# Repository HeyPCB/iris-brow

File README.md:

# Iris Brow

The forehead sensor strip of Iris: a VL53L1X distance sensor for vergence, an APDS-9306 light sensor, two I2S microphones 108 mm apart for sound direction and touch pads, on a brow-shaped board.

Part of [Iris, the human-eyed robot head](https://github.com/HeyPCB/iris), HeyPCB's open robot boards. Designed end to end with the HeyPCB method on
KiCad 10 (headless pipeline, Freerouting 2.4.1); every number below is measured on the files in this repository.
Mentions of `./run.sh`, `docs/rules/`, `blocks/` or `parts/` refer to the heypcb-kicad SDK that produced them.

| Layers | Outline | Parts | Nets | Connections routed | Vias | ERC errors | DRC errors / unconnected / parity |
|---|---|---|---|---|---|---|---|
| 2 | 116 x 12 mm, shaped | 20 | 11 | 45 -> 0 open | 33 | 0 | 0 / 0 / 0 |

**Not fabricated, assembled or powered.**

| | |
|---|---|
| KiCad project | [`kicad/`](kicad/) |
| Gerbers (unzipped and zipped), BOM, CPL, STEP, schematic PDF | [`fab/`](fab/) |
| Mechanism CAD, fit check and system docs | [Iris, the human-eyed robot head](https://github.com/HeyPCB/iris) |
| Renders | [top](media/top.png), [bottom](media/bottom.png) |
| Design process, every step as KiCad rendered it | [`media/design-process.mp4`](media/design-process.mp4) |

Iris Brow is the forehead sensor strip of **Iris**, an open-hardware robot head with human-like eyes. It
is board B4 of the Iris system spec v0.1 (section 4.3). The strip is 116 x 12 mm and sits behind the
forehead shell. It carries:
- a time-of-flight sensor for vergence distance;
- an ambient light sensor;
- two I2S microphones 108 mm apart, for the direction of a sound;
- a touch electrode.

One 8-pin JST SH harness connects it to the Cortex board (B1, ESP32-S3). It was designed with the HeyPCB
method on KiCad 10.0.6, by heypcb-kicad's headless pipeline with Freerouting 2.4.1, from the brief in
`board.json`.

**This board has not been fabricated, assembled or powered.** Everything below is what KiCad and the
pipeline measured on the design files. Nothing here has been tested on hardware or in the head. Gate
numbers come from `report.json`, positions and track lengths from
`coords.json` (written by `boards/iris_brow/coords.py`). Both come from the full run of
2026-10-03.

## Role in Iris

Iris has four board designs (spec section 4). B1 Cortex rides on the tilt cradle and runs the
ESP32-S3. B2 Brainstem is the power and servo hub. B3 is the iris LED ring, one in each eye. B4 Brow is
fixed to the forehead shell and adds what the eyes lack (spec section 4):

- **Distance for vergence.** The VL53L1X measures the distance d to the face in front of the robot.
  Firmware sets the vergence angle from it: vergence = 2 atan(39 / d) for the 78 mm IPD (spec section 8).
- **Ambient light.** It sets the brightness of the iris glow and the blink rate.
- **Stereo hearing for orienting saccades.** The two microphones are exactly 108 mm apart (head Y
  -54 and +54). That gives a maximum time difference of 0.31 ms, about 15 samples at 48 kHz (spec
  section 8, GCC-PHAT).
- **A forehead touch pad** for a "pat" reaction (ESP32-S3 TOUCH14).

## Features

- **ST VL53L1X** time-of-flight sensor (U1, VL53L1CXV0FY/1). It ranges up to 4 m with a field of view
  of up to 27 degrees, at up to 50 Hz (ST DocID031281 Rev 3, p.1 and Table 1). It sits on the centre
  line, on the face side.
  - ST's 100 nF and 4.7 uF are next to its AVDDVCSEL and AVSSVCSEL pins.
  - XSHUT is tied high through 10k, because it is not on the harness.
  - GPIO1 (the interrupt) is not connected, as the datasheet allows when it is unused.
- **Broadcom APDS-9306-065** ambient light sensor (U2), on the centre line above the ToF, with its
  datasheet 1 uF. Its INT output is not connected; firmware polls it.
- **Two TDK ICS-43434** bottom-port I2S microphones (MK1, MK2). They sit on the inside face and their
  0.5 mm sound ports open through the board at exactly x 4.0 and 112.0.
  - MK1 is MIC L (robot left). Its LR pin is low, so it answers in the **left** I2S slot.
  - MK2 is MIC R (robot right). Its LR pin is high, so it answers in the **right** slot.
  - Each has 100 nF at VDD and drives the shared SD line through 33 ohm.
- **Touch electrode:** two mirror-image 10 x 5 mm exposed copper pads (TP1 and TP2) on one TOUCH net,
  either side of the centre sensors. Espressif's keep-outs are board rule areas:
  - nothing on the opposite face;
  - a 1.5 mm gap to any ground or track;
  - a 0.15 mm trace.
- **J1:** JST SH 8-pin side-entry header SM08B-SRSS-TB, centred on the inside face with its mouth up.
  It is pinned exactly as the spec's BROW contract. A 10 uF bulk capacitor on 3V3 (C6) sits beside the
  ToF.
- **Board:**
  - a brow-shaped outline inside the binding 116 x 12 mm envelope, symmetric about the centre line;
  - 2 layers, 1.6 mm;
  - GND poured on both faces after routing;
  - four M2 holes at the binding positions.
- 20 footprints: 14 assembled parts, 2 copper touch pads (DNP), 4 holes. No regulator: 3V3 comes from
  the Cortex board.
- **3V3 load, from the datasheets** (a sum, not a measurement): about 19 mA on average, 41 mA at the
  ToF's emitter peaks. That is inside the contract's 50 mA. The parts are:
  - VL53L1X: 16-18 mA ranging average, peaks up to 40 mA (ST Table 16);
  - APDS-9306: 85 uA;
  - two ICS-43434: 490 uA each (TDK DS-000069, high-performance mode).

## Block diagram

```mermaid
flowchart LR
  B1["B1 Cortex: ESP32-S3<br/>J4 SH-8"]
  subgraph B4["B4 Iris Brow: 116 x 12 mm, 2 layers"]
    J1["J1 SM08B-SRSS-TB<br/>C6 10 uF on 3V3"]
    U1["U1 VL53L1X ToF<br/>I2C 0x29"]
    U2["U2 APDS-9306-065 ALS<br/>I2C 0x52"]
    MK1["MK1 ICS-43434, MIC L<br/>LR low: left slot"]
    MK2["MK2 ICS-43434, MIC R<br/>LR high: right slot"]
    TP["TP1 + TP2<br/>touch wings"]
  end
  B1 <-->|"BROW harness, 150 mm:<br/>3V3, GND, I2C, I2S, TOUCH"| J1
  J1 -->|"I2C_SDA, I2C_SCL, 3V3"| U1
  J1 -->|"I2C_SDA, I2C_SCL, 3V3"| U2
  J1 -->|"I2S_BCLK, I2S_WS, 3V3"| MK1
  J1 -->|"I2S_BCLK, I2S_WS, 3V3"| MK2
  MK1 -->|"SD via 33 ohm"| J1
  MK2 -->|"SD via 33 ohm"| J1
  TP -->|"TOUCH"| J1
```

## Sensor placement and windows

Board coordinates use the brief frame: mm from the board origin, x to the right and y down, seen from
the F face. Head coordinates use the spec's binding mapping (section 4.3):
- the F face is at X_H = +22.0 and faces the forehead shell;
- Y_H = x - 58;
- Z_H = 56 - y.

The shell's inner surface is at least 2.0 mm in front of the F face. Window sizes are the spec's
suggestions (section 4.3); the centres are measured from the built board.

| Feature | Board x, y (mm) | Head Y_H, Z_H (mm) | Face | Window in the shell (spec 4.3) | Where the centre comes from |
|---|---|---|---|---|---|
| VL53L1X package centre (U1) | 58.00, 6.00 | 0.00, 50.00 | F | one 6 x 3.5 mm slot centred here, or two 2.5 mm holes at the two points below | U1's placement |
| VL53L1X emitter (EMT, 0.70 mm aperture) | 56.48, 6.00 | -1.52, 50.00 | F | (inside the slot) | ST outline drawing through U1's placement |
| VL53L1X receiver (RTN, 0.85 mm lens) | 59.48, 6.00 | +1.48, 50.00 | F | (inside the slot) | ST outline drawing through U1's placement |
| APDS-9306 active area (U2) | 58.00, 2.12 | 0.00, 53.88 | F | 2 mm hole | Broadcom outline (0.223 mm off U2's centre at 58.00, 1.90) |
| MIC R sound port (MK2) | 4.00, 6.00 | -54.00, 50.00 | port through the board, part on B | 1.0 mm hole and a foam gasket ring | the footprint's 0.5 mm NPTH, measured |
| MIC L sound port (MK1) | 112.00, 6.00 | +54.00, 50.00 | port through the board, part on B | 1.0 mm hole and a foam gasket ring | the footprint's 0.5 mm NPTH, measured |
| Touch TP1 (robot right) | x 39.0-49.0, y 1.25-6.25 | Y -19.0 to -9.0, Z 54.75 to 49.75 | F, exposed copper | none (see *Check before ordering*) | pad copper, measured |
| Touch TP2 (robot left) | x 67.0-77.0, y 1.25-6.25 | Y +9.0 to +19.0, Z 54.75 to 49.75 | F, exposed copper | none | pad copper, measured |

**How the windows are marked on the board.** The SDK has no brief key for free drawings on the silk or
Fab layers, and its code was not changed. So each window is marked in four ways:
- **A named rule area on F.Cu that also bans the pour.** The F face therefore shows a bare-laminate
  patch of the window's shape round each sensor:
  - `window_tof_slot_6x3.5` (x 55.0-61.0, y 4.25-7.75; no via, no pour);
  - `window_als_d2` (2.4 mm circle at 58.00, 2.12; no via, no pour);
  - `window_mic_r_port_seal` and `window_mic_l_port_seal` (5 mm circles at the ports; no track, via
    or pour, so a gasket seals on flat mask).
- **The parts' own F.Fab outlines and values**, where the footprint has them.
- **The microphones' NPTH ports**, which go through the board.
- **The silk words "TOUCH"** beside the two pads.

"TOF" and "ALS" are in the brief's silk words, but found no free spot. A 0.8 mm word's text box is
1.47 mm tall, and the gap between the two sensors is 1.3 mm; capacitors and vias hold their other
sides. The drawing above and `coords.json` carry every number.

**Mounting and outline (binding positions kept).**
- Four 2.2 mm NPTH holes for M2 screws, at (12, 6), (34, 6), (82, 6) and (104, 6). In the head frame
  that is Y_H -46, -24, +24, +46 at Z_H +50.0. The screws go in from the B side into bosses on the shell,
  whose tips touch the F face.
- Copper, tracks and vias stay out of a 5.6 mm circle round each hole on both faces.
- The outline stays inside the spec's 116.0 x 12.0 mm envelope and is symmetric about x = 58.
  - Top edge: y = 1.0 ((x - 58) / 58)^2.
  - Bottom edge: y = 12 - 2.0 ((x - 58) / 58)^2.
  - Both are sampled every 14.5 mm and filleted (1000 mm and 600 mm on the shallow vertices, 2 mm at
    the four ends). So the strip is 12.0 mm tall at the centre and 9.0 mm at the ends.
  - The measured Edge.Cuts box is x -0.05 to 116.05 and y -0.04 to 12.03 (it includes the 0.1 mm
    line).
- **J1** is centred on the B face at (58.00, 3.35), with its mouth at y 0.73 (Z_H 55.27), so the plug
  enters from above (+Z). Pin 1 is at x 54.5 (Y_H -3.5) and pin 8 at x 61.5 (Y_H +3.5).

**Heights.** These come from the datasheets and the catalogue; none of them is a measurement.
- F face: VL53L1X 1.56 mm (the tallest; spec limit 1.6 mm), APDS-9306-065 0.65 mm, 0402 and 0603
  passives.
- B face: the SM08B-SRSS-TB body (the JLC row lists 2.9 mm and 4.32 mm), ICS-43434 0.98 mm (spec limit
  4.5 mm). `fab/iris_brow.step` has the board with KiCad's 3D bodies. U2 has no body:
  KiCad 10.0.6 ships no model for `OptoDevice:Broadcom_DFN-6_2x2mm_P0.65mm`.

## Pinout: J1 to Cortex J4 (spec section 5, BROW, binding)

JST SH 8-pin, SM08B-SRSS-TB (C160407). Pin n is pad n of the KiCad footprint. The harness is
double-ended, same direction (pin n to pin n), 28 AWG, 150 mm. The board nets below were read back from
the run's `build/iris_brow/design.json`.

| Pin | Net | Dir | Level / type | On this board |
|---|---|---|---|---|
| 1 | 3V3 | B1 -> B4 | 3.3 V, at most 50 mA (source B1 U2) | U1 AVDD/AVDDVCSEL, U2 VDD, MK1/MK2 VDD, MK2 LR, XSHUT pull-up, C6 10 uF |
| 2 | GND | | | ground; J1's two mounting pads are GND too |
| 3 | I2C_SDA | <-> | 3.3 V open drain, 400 kHz | U1 pin 9, U2 pin 2. No pull-up here: 2.2 k on B1 only |
| 4 | I2C_SCL | B1 -> | 3.3 V open drain | U1 pin 10, U2 pin 1 |
| 5 | I2S_BCLK | B1 -> B4 | 3.3 V, 3.072 MHz | MK1 and MK2 SCK |
| 6 | I2S_WS | B1 -> B4 | 3.3 V, 48 kHz | MK1 and MK2 WS |
| 7 | I2S_MIC_SD | B4 -> B1 | 3.3 V, tri-stated per slot | MK1 and MK2 SD, each through 33 ohm. The 100 k pull-down is on B1 (GPIO40) |
| 8 | TOUCH | B4 -> B1 | analog, capacitive | TP1 and TP2 (B1 GPIO14, TOUCH14) |

## I2C addresses and I2S slots

| Device | Board | 7-bit address | Note |
|---|---|---|---|
| INA226 | B2 | 0x40 | spec section 4.3 |
| VL53L1X (U1) | B4 | **0x29** | ST writes it as **0x52**, the 8-bit write address (datasheet section 4, Figure 12). Use 0x29 in a 7-bit API, or it lands on the APDS-9306 |
| APDS-9306-065 (U2) | B4 | **0x52** | fixed ("single slave address of 0X52 hex using 7-bit addressing", Broadcom AV02-4755EN) |

No two addresses collide. The camera's SCCB is on its own pins on B1.

| Microphone | Position | LR | I2S slot |
|---|---|---|---|
| MK1, MIC L | robot left, Y_H +54.0 | GND | left: data after WS falls |
| MK2, MIC R | robot right, Y_H -54.0 | 3V3 | right: data after WS rises |

Each frame has 64 SCK cycles (TDK DS-000069), so BCLK is 48 kHz x 64 = 3.072 MHz.

## Departures from the spec

| Spec (section 4.3) | On the board | Why |
|---|---|---|
| Rectangle, 116.0 x 12.0 mm, fillet 2.0 | A brow-shaped outline inside the same envelope (12 mm tall at the centre, 9 mm at the ends), with the same holes | The task asked for a gently shaped brow strip. Anything drawn for the rectangle still clears it |
| Touch electrode at x 40-52, masked F copper, with a ground-hatched ring | Two 10 x 5 mm exposed pads at x 39-49 and 67-77; no pour within 1.5 mm, nothing on B under them, solid GND pour beyond | Symmetry: a pat anywhere across the middle of the forehead lands on it. The shell is at least 2.0 mm in front of the board, and Espressif says to remove air gaps or bridge them with springs, which needs an exposed pad. KiCad's stock wire and test pads all open the mask. The SDK pours solid copper only, so there is no hatched ring |
| APDS-9306 at x 65-67 | At x 58 (centre line), y 1.9, above the ToF | A symmetric layout about the centre line |
| J1 at x 86-98 on B | Centred on B (x 52-64), mouth up | A symmetric B face, equal I2S runs to both microphones, and the shortest harness path |
| Microphone SD pins tied directly (datasheet stereo figure) | 33 ohm source resistor on each | KiCad types SD as an output, so ERC refuses two on one net. The resistor also damps the shared line |
| ICS-43434 orientation not stated | Ports outboard, pads inboard | The pads face the rest of the board. Routing closed only once each microphone's bypass capacitor had its GND pad beside the port's GND ring (MIC R's LR pin is 3V3, so its ring has no other GND neighbour) |
| (not in the spec) | 10 uF on 3V3 | Bulk at the end of the 150 mm cable for the ToF's emitter pulses (40 mA peak, ST Table 16) |

## Measured gates (full run with media, 2026-10-03, from `report.json`)

| Gate | Result |
|---|---|
| Composition | 7 block instances (6 distinct blocks, all new, prefixed `brow_`): 20 parts, 11 nets, 4 no-connects (U1 GPIO1, U1 DNC, U2 INT, U2 NC) |
| Part binding (`parts/lcsc_pinned.json`) | 14 of 14 orderable parts bound, 0 unsourced, 0 identity conflicts. H1-H4 are not in the BOM; TP1 and TP2 are DNP (copper only). 4 distinct Extended parts (C160407, C190004, C2649498, C5656610), about $12 in JLC loading fees |
| ERC (`kicad-cli sch erc --severity-all`) | **0 errors, 0 warnings** |
| Netlist round trip | **identical**, 11 nets |
| Freerouting, rung 1, fanout off (kept) | 45 -> 4 open (all GND). The last-mile router closed all 4, and DRC kept them: **0 open** |
| Freerouting, rung 1, fanout on (for comparison) | 45 -> 8 open; the last mile closed 5, so 3 open |
| Copper | 204 tracks, 28 routing vias, 732.5 mm of track (B.Cu 467.8 mm, F.Cu 264.7 mm). No net class was narrowed |
| Pours (only after a measured 0 open) | GND on F.Cu and B.Cu, 5 stitching vias (33 vias in all). 0 open after the pour, after stitching and at the end |
| Silkscreen | 3 words placed (TOUCH, TOUCH, BROW); the 4 title lines on B; 12 designators re-seated and 5 hidden; 0 stitching vias displaced |
| DRC (`--severity-all --schematic-parity`, KiCad 10.0.6) | fresh, **0 errors, 0 warnings, 0 unconnected, 0 parity** |
| DFM (`jlcpcb_2layer`) | **0 errors**, 1 warning: 45 stock-footprint silk strokes at 0.12 mm, which the fab prints at its 0.15 mm minimum |
| Fab gate | **ready**, no blockers. Two copper gerbers; the gerber job has `LayerNumber` 2 and a 1.6 mm board. The BOM has 10 rows and 14 parts; the JLC CPL lists 14 parts (7 on the bottom) and corrected 4 rotations |
| Media | 63 3D frames, the renders, and a 97.7 s video (142 frames) |

Routing depends on the last mile. Freerouting alone left four GND connections open, all at the
microphones: MK1's port ring, LR pin and bypass capacitor, MK2's port ring, and a 47.7 mm link from C4
back to the centre. The brief routes the same way every run (`docs/rules/pipeline.md`, "One brief routes
one way"). All three routing runs after the last placement change (two `--no-media` runs and the full
run) routed 45 -> 0.

Routed lengths (`coords.json`):

| Net | Length (B.Cu + F.Cu) | Vias |
|---|---|---|
| TOUCH | 30.0 mm (2.0 + 28.0) | 1 |
| I2S_BCLK | 121.3 mm (98.9 + 22.4) | 4 |
| I2S_WS | 124.6 mm (68.7 + 55.9) | 4 |
| I2S_MIC_SD | 113.2 mm (113.2 + 0) and 1.6 mm from each microphone to its 33 ohm | 0 |
| I2C_SDA / I2C_SCL | 12.0 / 21.9 mm | 2 / 2 |
| 3V3 | 159.4 mm | 8 |

## Check these before ordering

The board passes ERC, the netlist round trip, routing, DRC (errors, unconnected and parity), DFM and the
fab gate in KiCad. It has not been fabricated, assembled, powered or fitted to a head.

**Microphones**
- **The ICS-43434 is end of life.** TDK's product page marks it "EOL"
  (https://invensense.tdk.com/products/ics-43434/), and it names no replacement.
  - JLC stock on 2026-10-03 was **3 807** (C5656610, live lookup). Buy both microphones, plus spares,
    with the first order.
  - **The alternative is the spec's: Infineon IM69D120V01**, C3171853, 282 in stock on 2026-10-03.
    It is a PDM microphone, so it is not a drop-in:
    - a different package, footprint and pinout;
    - I2S0 on the ESP32-S3 must run in PDM receive mode;
    - this board needs a respin with a new `brow_mic_*` block.
- **SD line load.** TDK designed the SD output to drive 85 pF (DS-000069, "SD output drive strength").
  The load is:
  - 113.2 mm of SD copper on this board;
  - the other microphone's tri-stated pin (about 6 pF, same section);
  - the 150 mm harness;
  - B1's trace and the ESP32-S3 input.

  Check the edges with a scope on the first board.
- **The servos are loud:** 65 +- 5 dB at 30 cm each (spec section 2.7), so the spec gates sound
  localisation during servo moves (section 8).
- **The ports need the shell's 1.0 mm holes**, aligned to x 4.0 and 112.0, with a gasket. The 5 mm
  circles round the ports are flat mask for it.

**VL53L1X cover and crosstalk**
- **ST's ranging figures assume no cover glass** (DocID031281 Rev 3, section 3.1, test conditions).
  Whatever covers the sensor, the shell must keep ST's exclusion cones clear. Those cones are "kept free
  of mechanical items" (outline drawing, page 2, note 4):
  - receiver: 39.60 degrees full angle, 1.08 mm across at the module's top face;
  - emitter: 36.50 degrees, 0.84 mm across.
- **Derived from those cones** (not measured): at a height h above the module's top, the receiver
  cone is 1.08 + 0.720 h mm across and the emitter cone 0.84 + 0.660 h mm.
  - The module top is 1.56 mm above the F face, and the shell's inner face 2.0 mm above it, so h = 0.44
    mm at the shell's inner face: 1.40 mm (receiver) and 1.13 mm (emitter).
  - The spec's **6 x 3.5 mm slot** (straight walls, centred at x 58.00) clears both cones through a shell
    up to **2.28 mm** thick.
  - The spec's alternative, **two 2.5 mm holes** at the emitter and receiver, clips the receiver's cone
    in a shell thicker than **1.53 mm**, and leaves a 0.5 mm web between the holes.
- **An open slot avoids cover crosstalk.** An IR-transparent cover reflects part of the emitter's
  pulse straight into the receiver. If the shell needs a cover:
  - add a light barrier between the emitter and receiver windows;
  - calibrate crosstalk and offset in firmware;
  - measure it on the printed forehead (spec, open question 6).
- **I/O level.** The driver runs the pads in 1V8 mode by default; on this 3.3 V bus firmware must set
  2V8 mode (ST Table 14, notes 3-4; spec section 4.3, register 0x2E bit 0).

**Touch electrode**
- **The air gap.** The shell is at least 2.0 mm in front of the pads. Espressif: "any air gaps between
  the sensor pad and overlay must be eliminated", or "compressed metal springs can be used". Plan one of
  these:
  - a touch spring or conductive foam on each pad (the pads are bare for this);
  - a copper-tape electrode on the shell's inside, wired to a pad.
- **Size.** Each pad is 10 x 5 mm with rounded corners, about the area of a 7.9 mm circle. That is just
  under Espressif's 8-15 mm electrode range; the two pads together are about an 11 mm circle. They are
  one electrode: a palm covers both.
- **Ground and spacing differ from Espressif's guidance** (ESP32-S3 hardware design guidelines; the
  esp-iot-solution touch design note).
  - Done as advised: no copper under the pads on B, ground pour at least 1.5 mm away on F, a 0.15 mm
    trace, and 30.0 mm of TOUCH copper on this board (the limit is 300 mm, including the harness and
    B1).
  - Not as advised:
    - the pour beyond the gap is solid, not hatched;
    - the trace-to-ground gap is 0.35 mm, not 0.5-1 mm, because J1's pads 7 and 8 are 0.40 mm apart.
  - Measured on the board: on the same layer, the TOUCH copper is at least 2.83 mm from I2S_BCLK and
    2.33 mm from I2C_SCL.
  - The TOUCH track crosses the board's middle on F between the ALS and the ToF (y 3.75), so a touch
    near the centre of the forehead also counts. Check the readings while the ToF ranges: the track
    passes about 1.1 mm from the ToF's emitter supply pins.
- **B1 needs the series resistor.** Espressif recommends 470 ohm to 2 kohm (510 ohm) within 1 mm of the
  touch pin. That belongs on the Cortex board at GPIO14; the spec's GPIO table does not list it.

**Assembly and mechanics**
- **Two-sided assembly.**
  - Top: U1, U2, C1-C3, C6, R1.
  - Bottom: J1, MK1, MK2, C4, C5, R2, R3.
  - The JLC CPL marks the bottom parts as Bottom. TP1 and TP2 are DNP: bare copper, nothing placed.
- **No 3D body for U2.** KiCad 10.0.6 ships no model for its footprint, so the renders and the STEP
  show bare pads there. Use the datasheet's 2.0 x 2.0 x 0.65 mm.
- **J1's mouth is 0.73 mm inside the top edge, and the cable leaves upward (+Z) at the head's centre
  line.** Route the 150 mm BROW cable over the upper-lid servo column. The spec put J1 at Y_H +28 to
  +40; check the cable path in CAD.
- **Stackup.** The gerber job lists KiCad's default 2-layer stackup (35 um copper, 1.51 mm FR4,
  1.6 mm). The fab's real stackup is chosen when ordering.

**Sourcing**
- The 10 part numbers in `fab/iris_brow_bom.csv` all come from
  `parts/lcsc_pinned.json`. This board added five rows on 2026-10-03 from live `heypcb parts lookup`
  reads:
  - C190004 VL53L1CXV0FY/1, 12 199 in stock;
  - C2649498 APDS-9306-065, 5 253;
  - C160407 SM08B-SRSS-TB(LF)(SN), 267 231;
  - C19666 4.7 uF 0603, Basic;
  - C25105 33 ohm 0402, Basic.

  The ICS-43434 row (C5656610) was pinned earlier, on 2026-10-02. Stock and Basic/Extended class go
  stale; re-check on jlcpcb.com before ordering.

## Files

In this folder (committed):
- `board.json`: the brief.
- `coords.py`: measures the mechanical numbers above from the built board and draws the window map.
- `img/`:
  - `iris_brow_face_side.png`, `iris_brow_inner_side.png` and `iris_brow_angled.png`: KiCad 10 raytraced
    renders;
  - `iris_brow_windows.svg`: the window map, a copy of `windows.svg`.

The blocks are `blocks/brow_*.json`; the part rows are in `parts/lcsc_pinned.json`.

Under `build/iris_brow/` (regenerated, not committed):
- `report.json`: the gate report.
- `coords.json` and `windows.svg`.
- `iris_brow.kicad_sch` and `iris_brow.kicad_pcb`.
- `fab/`:
  - `iris_brow_gerbers.zip`;
  - `iris_brow_bom.csv`;
  - `iris_brow_cpl_jlc.csv`;
  - `iris_brow_pos.csv`;
  - `iris_brow_schematic.pdf`;
  - `iris_brow.step`.
- `media/design-process.mp4`.

## Reproduce

From the heypcb-kicad repository:

```bash
./run.sh --board boards/iris_brow              # every stage, with the renders and the video (about 7 min)
./run.sh --board boards/iris_brow --no-media   # stop before the 3D frames, renders and video (about 2 min)
"${KICAD_APP:-/Applications/KiCad/KiCad.app}/Contents/Frameworks/Python.framework/Versions/Current/bin/python3" \
    boards/iris_brow/coords.py   # KiCad's Python, as run.sh picks it: positions, windows, track lengths
```

Clear `build/iris_brow/frames` and `build/iris_brow/render` before a full run, or the video replays
earlier runs (`docs/rules/pipeline.md`).

## Licence and sources

The Iris Brow hardware design (the brief, the `brow_*` blocks, `coords.py`, the renders and this README)
is licensed under the **CERN Open Hardware Licence Version 2, Strongly Reciprocal (CERN-OHL-S-2.0)**,
https://ohwr.org/cern_ohl_s_v2.txt, as the Iris spec states for all Iris hardware. KiCad's symbols,
footprints and 3D models are CC-BY-SA-4.0 with the KiCad library exception. No datasheet is copied
here; each fact above cites its source:

- ST VL53L1X datasheet, DocID031281 Rev 3. Pins (Table 2), the application schematic and its notes
  (Figure 3), address 0x52 (section 4, Figure 12), I/O modes (Table 14), current (Table 16), and the
  outline and exclusion cones (Figures 18-19): https://www.st.com/resource/en/datasheet/vl53l1x.pdf
- Broadcom APDS-9306/APDS-9306-065 datasheet, AV02-4755EN. Pins (p.2), supply and current (p.3), 7-bit
  address 0x52, the application circuit with 1 uF (p.15), and the outline with its active-area offset
  (p.18): https://docs.broadcom.com/docs/AV02-4755EN
- TDK InvenSense ICS-43434 datasheet, DS-000069. Pins and LR, 0.1 uF, the SD pull-down (Table 8), 64 SCK
  per frame, and the 85 pF SD drive:
  https://www.cdiweb.com/datasheets/invensense/ds-000069-ics-43434-v1.0-2.pdf. EOL status: https://invensense.tdk.com/products/ics-43434/
- Espressif, ESP32-S3 hardware design guidelines, Touch Sensor (electrode 8-15 mm, trace at most 0.18 mm
  and 300 mm, 0.5-1 mm to ground, hatched ground):
  https://docs.espressif.com/projects/esp-hardware-design-guidelines/en/latest/esp32s3/pcb-layout-design.html
- Espressif, touch sensor design note (esp-iot-solution release/v1.0): ground plane (section 3.3.7), air
  gaps and springs (section 3.1.1), and the series resistor:
  https://github.com/espressif/esp-iot-solution/blob/release/v1.0/documents/touch_pad_solution/touch_sensor_design_en.md
- The Iris system spec v0.1 (not published): sections 2.6, 4.3, 4.5, 5, 6, 8 and 10. Its binding
  contracts are in [the Iris system docs](https://github.com/HeyPCB/iris/blob/main/docs/system.md).

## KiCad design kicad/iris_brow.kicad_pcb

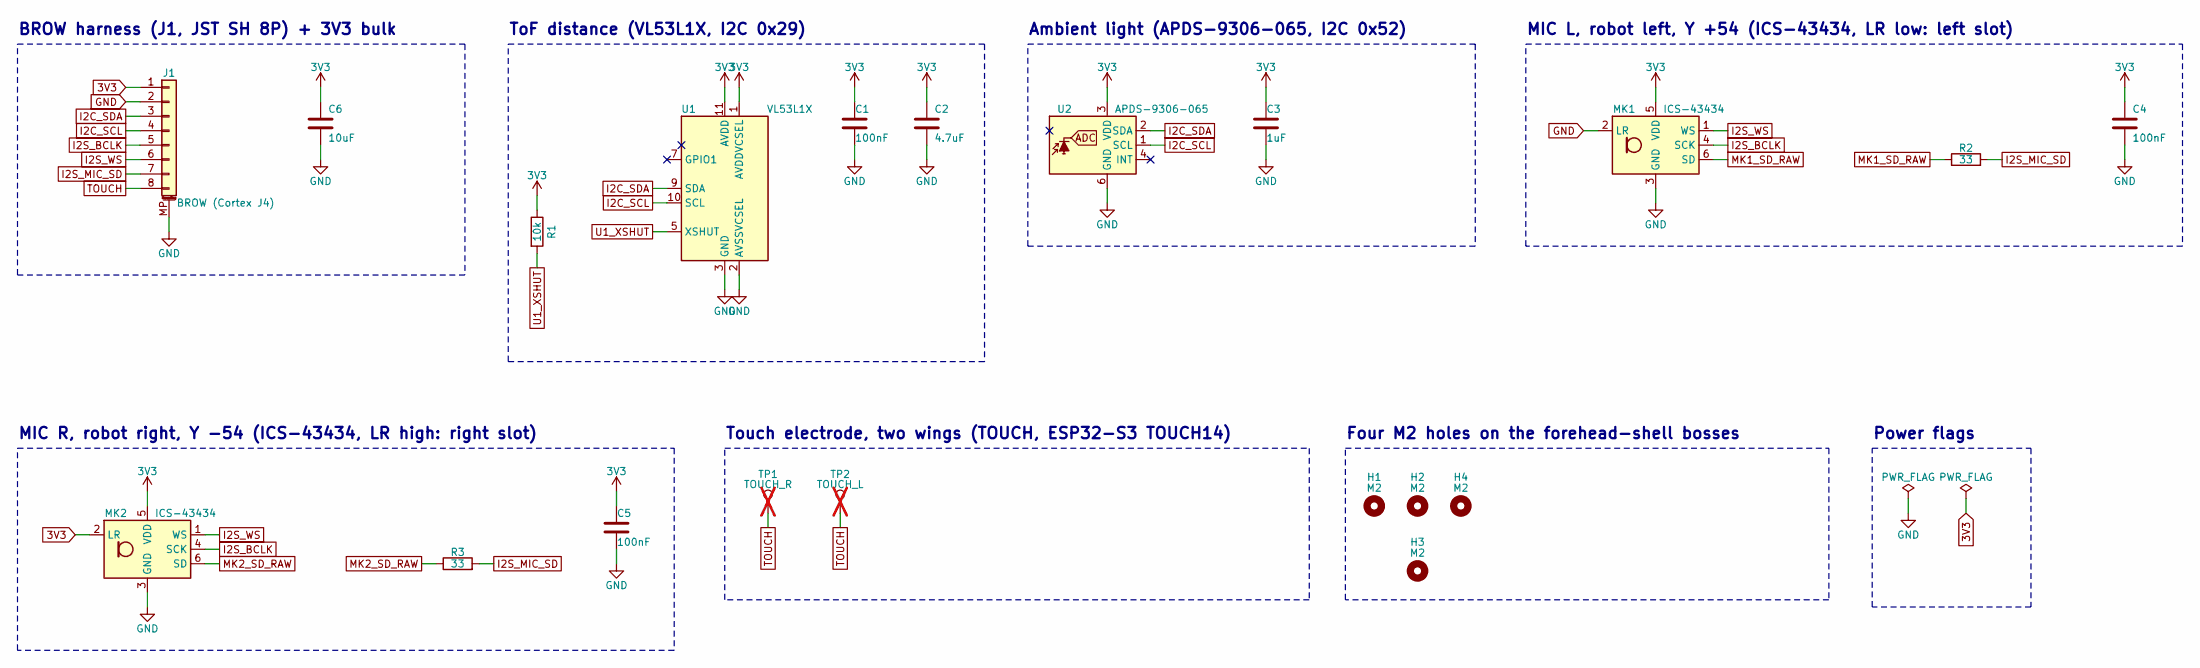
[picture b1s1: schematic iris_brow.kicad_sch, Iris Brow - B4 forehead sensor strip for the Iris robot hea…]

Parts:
C1, C4, C5: 100nF; C_0402_1005Metric; MPN CL05B104KO5NNNC; LCSC C1525
C2: 4.7uF; C_0603_1608Metric; MPN CL10A475KO8NNNC; LCSC C19666
C3: 1uF; C_0402_1005Metric; MPN CL05A105KA5NQNC; LCSC C52923
C6: 10uF; C_0603_1608Metric; MPN CL10A106MA8NRNC; LCSC C96446
H1, H2, H3, H4: M2; MountingHole_2.2mm_M2
J1: BROW (Cortex J4); JST_SH_SM08B-SRSS-TB_1x08-1MP_P1.00mm_Horizontal; MPN SM08B-SRSS-TB(LF)(SN); LCSC C160407
MK1, MK2: ICS-43434; InvenSense_ICS-43434-6_3.5x2.65mm; MPN ICS-43434; LCSC C5656610
R1: 10k; R_0402_1005Metric; MPN 0402WGF1002TCE; LCSC C25744
R2, R3: 33; R_0402_1005Metric; MPN 0402WGF330JTCE; LCSC C25105
TP1: TOUCH_R; SolderWirePad_1x01_SMD_5x10mm; not fitted
TP2: TOUCH_L; SolderWirePad_1x01_SMD_5x10mm; not fitted
U1: VL53L1X; ST_VL53L1x; MPN VL53L1CXV0FY/1; LCSC C190004
U2: APDS-9306-065; Broadcom_DFN-6_2x2mm_P0.65mm; MPN APDS-9306-065; LCSC C2649498

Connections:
3V3: C1.1, C2.1, C3.1, C4.1, C5.1, C6.1, J1.1, MK1.5 (VDD), MK2.2 (LR), MK2.5 (VDD), R1.1, U1.1 (AVDDVCSEL), U1.11 (AVDD), U2.3 (VDD)
GND: C1.2, C2.2, C3.2, C4.2, C5.2, C6.2, J1.2, J1.MP (MountPin), MK1.2 (LR), MK1.3 (GND), MK2.3 (GND), U1.2 (AVSSVCSEL), U1.3 (GND), U1.4 (GND), U1.6 (GND), U1.12 (GND), U2.6 (GND)
I2C_SCL: J1.4, U1.10 (SCL), U2.1 (SCL)
I2C_SDA: J1.3, U1.9 (SDA), U2.2 (SDA)
I2S_BCLK: J1.5, MK1.4 (SCK), MK2.4 (SCK)
I2S_MIC_SD: J1.7, R2.2, R3.2
I2S_WS: J1.6, MK1.1 (WS), MK2.1 (WS)
MK1_SD_RAW: MK1.6 (SD), R2.1
MK2_SD_RAW: MK2.6 (SD), R3.1
TOUCH: J1.8, TP1.1, TP2.1
U1_XSHUT: R1.2, U1.5 (XSHUT)

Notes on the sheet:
BROW harness (J1, JST SH 8P) + 3V3 bulk
ToF distance (VL53L1X, I2C 0x29)
Ambient light (APDS-9306-065, I2C 0x52)
MIC L, robot left, Y +54 (ICS-43434, LR low: left slot)
MIC R, robot right, Y -54 (ICS-43434, LR high: right slot)
Touch electrode, two wings (TOUCH, ESP32-S3 TOUCH14)
Four M2 holes on the forehead-shell bosses
Power flags

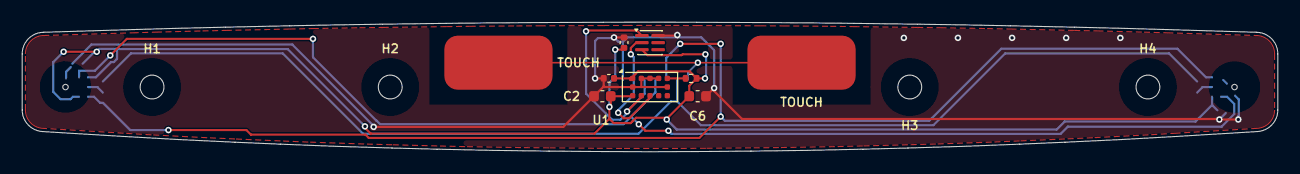
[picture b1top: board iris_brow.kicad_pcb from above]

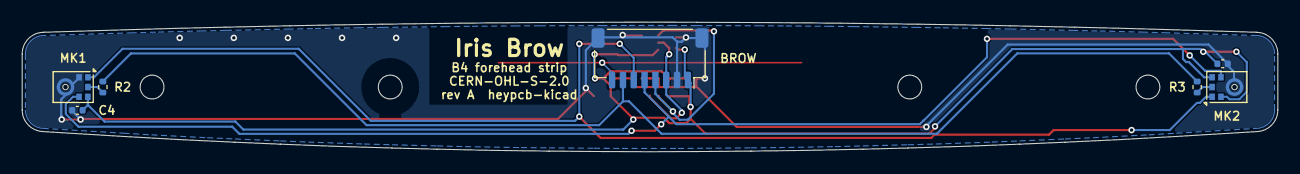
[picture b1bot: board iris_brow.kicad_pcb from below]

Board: 2 copper layers, 116.0 x 12.0 mm, 20 parts (7 on the bottom side), 11 nets.

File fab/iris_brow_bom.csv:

"Reference","Value","Footprint","MPN","LCSC","Qty"
"C1,C4,C5","100nF","Capacitor_SMD:C_0402_1005Metric","CL05B104KO5NNNC","C1525","3"
"C2","4.7uF","Capacitor_SMD:C_0603_1608Metric","CL10A475KO8NNNC","C19666","1"
"C3","1uF","Capacitor_SMD:C_0402_1005Metric","CL05A105KA5NQNC","C52923","1"
"C6","10uF","Capacitor_SMD:C_0603_1608Metric","CL10A106MA8NRNC","C96446","1"
"J1","BROW (Cortex J4)","Connector_JST:JST_SH_SM08B-SRSS-TB_1x08-1MP_P1.00mm_Horizontal","SM08B-SRSS-TB(LF)(SN)","C160407","1"
"MK1,MK2","ICS-43434","Sensor_Audio:InvenSense_ICS-43434-6_3.5x2.65mm","ICS-43434","C5656610","2"
"R1","10k","Resistor_SMD:R_0402_1005Metric","0402WGF1002TCE","C25744","1"
"R2,R3","33","Resistor_SMD:R_0402_1005Metric","0402WGF330JTCE","C25105","2"
"U1","VL53L1X","Sensor_Distance:ST_VL53L1x","VL53L1CXV0FY/1","C190004","1"
"U2","APDS-9306-065","OptoDevice:Broadcom_DFN-6_2x2mm_P0.65mm","APDS-9306-065","C2649498","1"
